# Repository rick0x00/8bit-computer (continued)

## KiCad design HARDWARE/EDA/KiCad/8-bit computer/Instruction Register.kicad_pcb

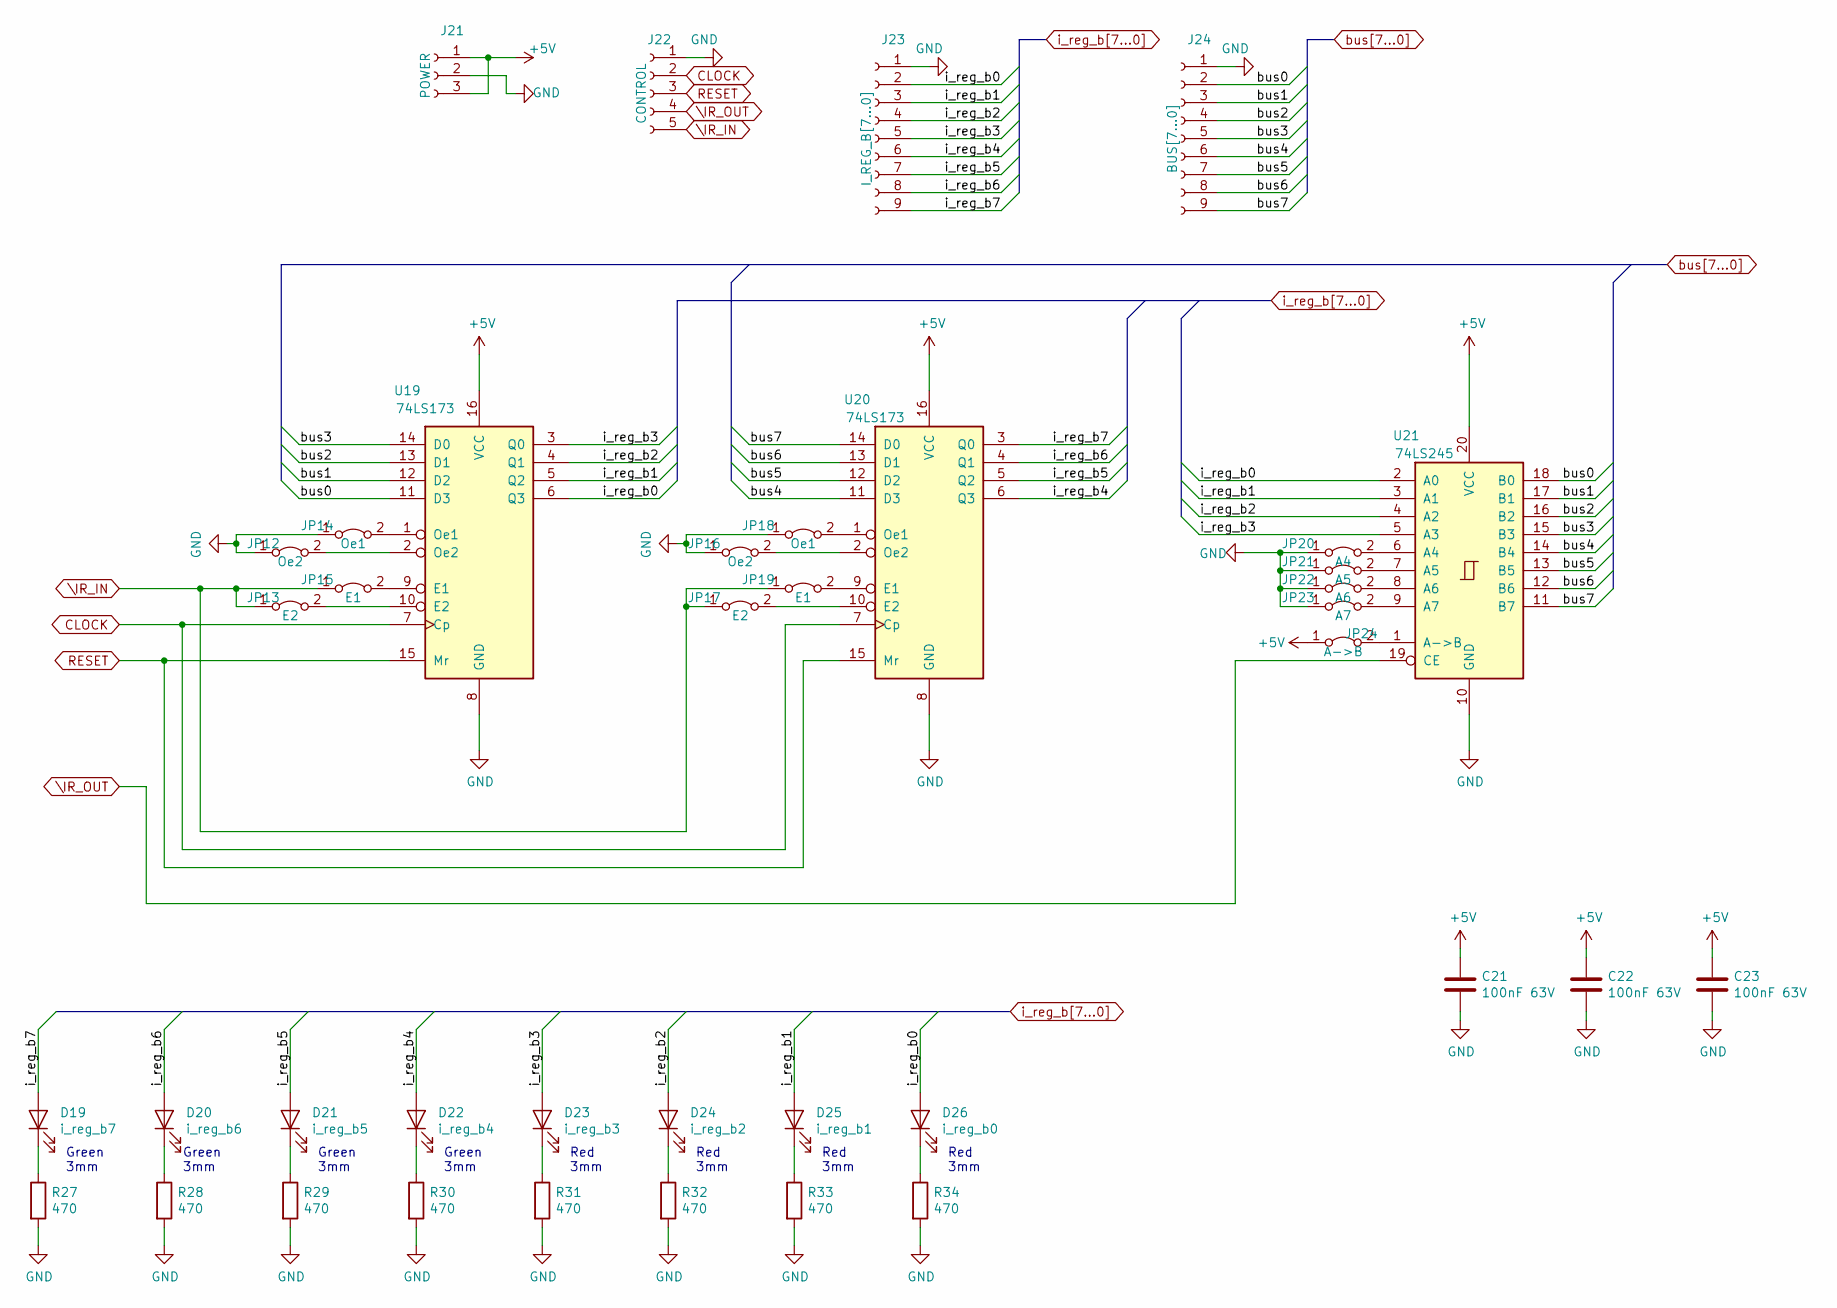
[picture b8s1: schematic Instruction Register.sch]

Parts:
C21, C22, C23: 100nF 63V; C_Rect_L7.0mm_W2.5mm_P5.00mm
D19: i_reg_b7; LED_D3.0mm
D20: i_reg_b6; LED_D3.0mm
D21: i_reg_b5; LED_D3.0mm
D22: i_reg_b4; LED_D3.0mm
D23: i_reg_b3; LED_D3.0mm
D24: i_reg_b2; LED_D3.0mm
D25: i_reg_b1; LED_D3.0mm
D26: i_reg_b0; LED_D3.0mm
J21: POWER; PinSocket_1x03_P2.00mm_Vertical
J22: CONTROL; PinSocket_1x05_P2.00mm_Vertical
J23: I_REG_B[7...0]; PinSocket_1x09_P2.00mm_Vertical
J24: BUS[7...0]; PinSocket_1x09_P2.00mm_Vertical
JP12, JP16: Oe2; TestPoint_2Pads_Pitch2.54mm_Drill0.8mm
JP13, JP17: E2; TestPoint_2Pads_Pitch2.54mm_Drill0.8mm
JP14, JP18: Oe1; TestPoint_2Pads_Pitch2.54mm_Drill0.8mm
JP15, JP19: E1; TestPoint_2Pads_Pitch2.54mm_Drill0.8mm
JP20: A4; TestPoint_2Pads_Pitch2.54mm_Drill0.8mm
JP21: A5; TestPoint_2Pads_Pitch2.54mm_Drill0.8mm
JP22: A6; TestPoint_2Pads_Pitch2.54mm_Drill0.8mm
JP23: A7; TestPoint_2Pads_Pitch2.54mm_Drill0.8mm
JP24: A->B; TestPoint_2Pads_Pitch2.54mm_Drill0.8mm
R27, R28, R29, R30, R31, R32, R33, R34: 470; R_Axial_DIN0207_L6.3mm_D2.5mm_P7.62mm_Horizontal
U19, U20: 74LS173; DIP-16_W7.62mm_LongPads
U21: 74LS245; DIP-20_W7.62mm_LongPads

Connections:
+5V: C21.1, C22.1, C23.1, J21.1, J21.3, JP24.1 (A), U19.16 (VCC), U20.16 (VCC), U21.20 (VCC)
CLOCK: J22.2, U19.7 (Cp), U20.7 (Cp)
GND: C21.2, C22.2, C23.2, J21.2, J22.1, J23.1, J24.1, JP12.1 (A), JP14.1 (A), JP16.1 (A), JP18.1 (A), JP20.1 (A), JP21.1 (A), JP22.1 (A), JP23.1 (A), R27.2, R28.2, R29.2, R30.2, R31.2, R32.2, R33.2, R34.2, U19.8 (GND), U20.8 (GND), U21.10 (GND)
unnamed: D19.1 (K), R27.1
unnamed: D20.1 (K), R28.1
unnamed: D21.1 (K), R29.1
unnamed: D22.1 (K), R30.1
unnamed: D23.1 (K), R31.1
unnamed: D24.1 (K), R32.1
unnamed: D25.1 (K), R33.1
unnamed: D26.1 (K), R34.1
unnamed: JP12.2 (B), U19.2 (Oe2)
unnamed: JP13.2 (B), U19.10 (E2)
unnamed: JP14.2 (B), U19.1 (Oe1)
unnamed: JP15.2 (B), U19.9 (E1)
unnamed: JP16.2 (B), U20.2 (Oe2)
unnamed: JP17.2 (B), U20.10 (E2)
unnamed: JP18.2 (B), U20.1 (Oe1)
unnamed: JP19.2 (B), U20.9 (E1)
unnamed: JP20.2 (B), U21.6 (A4)
unnamed: JP21.2 (B), U21.7 (A5)
unnamed: JP22.2 (B), U21.8 (A6)
unnamed: JP23.2 (B), U21.9 (A7)
unnamed: JP24.2 (B), U21.1 (A->B)
RESET: J22.3, U19.15 (Mr), U20.15 (Mr)
\IR_IN: J22.5, JP13.1 (A), JP15.1 (A), JP17.1 (A), JP19.1 (A)
\IR_OUT: J22.4, U21.19 (CE)
bus0: J24.2, U19.11 (D3), U21.18 (B0)
bus1: J24.3, U19.12 (D2), U21.17 (B1)
bus2: J24.4, U19.13 (D1), U21.16 (B2)
bus3: J24.5, U19.14 (D0), U21.15 (B3)
bus4: J24.6, U20.11 (D3), U21.14 (B4)
bus5: J24.7, U20.12 (D2), U21.13 (B5)
bus6: J24.8, U20.13 (D1), U21.12 (B6)
bus7: J24.9, U20.14 (D0), U21.11 (B7)
i_reg_b0: D26.2 (A), J23.2, U19.6 (Q3), U21.2 (A0)
i_reg_b1: D25.2 (A), J23.3, U19.5 (Q2), U21.3 (A1)
i_reg_b2: D24.2 (A), J23.4, U19.4 (Q1), U21.4 (A2)
i_reg_b3: D23.2 (A), J23.5, U19.3 (Q0), U21.5 (A3)
i_reg_b4: D22.2 (A), J23.6, U20.6 (Q3)
i_reg_b5: D21.2 (A), J23.7, U20.5 (Q2)
i_reg_b6: D20.2 (A), J23.8, U20.4 (Q1)
i_reg_b7: D19.2 (A), J23.9, U20.3 (Q0)

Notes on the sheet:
Green 3mm
Red 3mm

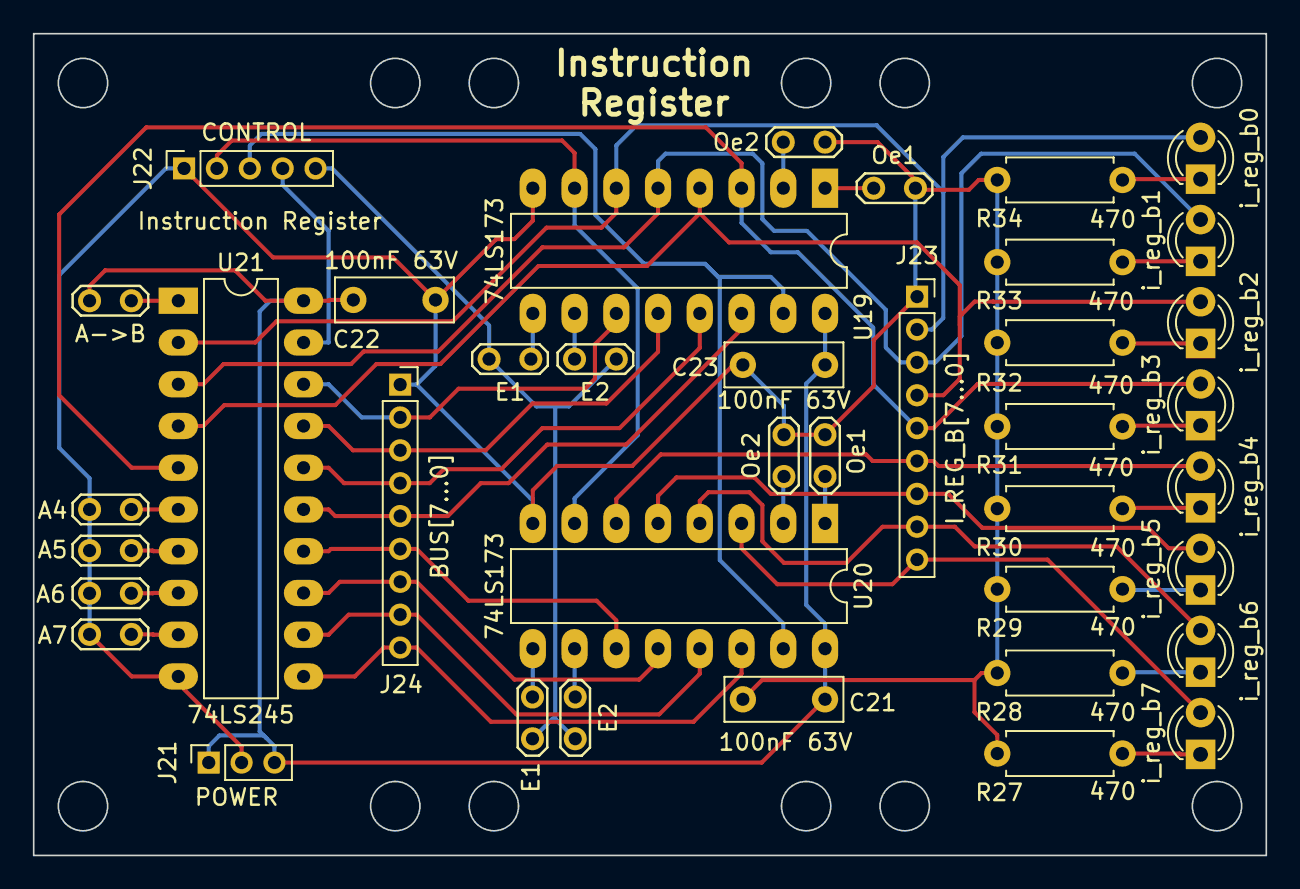
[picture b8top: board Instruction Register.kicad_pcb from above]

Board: 2 copper layers, 75.0 x 50.0 mm, 39 parts (0 on the bottom side), 43 nets.

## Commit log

2021-08-03 Upload Files
2021-08-03 add image and credits
